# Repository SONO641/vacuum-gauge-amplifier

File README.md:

# amplifier board for thermocouple vacuum gauge

### Description of the control board for vacuum thermocouple gauge.

I found <a href="http://www.belljar.net/tcgauge.htm">
this tutorial</a>  about the operating principle of thermocouple vacuum gauges. I designed the board below based on the article. 

A thermocouple vacuum gauge works by heating a filament at a constant current. The filament’s temperature is higher at a lower pressure because it only loses heat by radiation. The temperature is lower at higher pressure because of the heat loss via the convection of gas in addition to radiation. A thermocouple reads the filament’s temperature and produces a DC signal a function of the temperature difference from the end of the wire. For the gauge I used (KJL-1518) maximum thermocouple voltage is 10mV. I used an instrument amplifier (INA128) to amplify the mV signal by a factor of 330.

The circuit has two parts. One is to supply current to the filament. I used LM317 to limit the current to 16mA. The 5V DC supply for the filament has to be isolated, otherwise thermocouple won't work. I used another DC-DC converter for the instrument amplifier to supply ±9V for INA128. Using this setup, a few mtorr pressure gives 3.7V and 100mtorr 1V between SIG and REF pins. Calibrate the gauve following the artible above.  

A commercial thermocouple gauge controller costs about USD 700 with a display and serial output. Parts for the amplifier board was about USD 25. I use ADS1115 to measure analog signals, and a Raspberry Pi to communicate and log the pressure to a server. Total cost was under USD 100. 

Connect filament +/- to gauge pins 1 and 7, and TC gauge +/- to pin 5/3 of the thermocouple gauge. Apply 5V DC voltage between VIN and GND. Measure voltage between SIG and REF. Applying 5V to enable (EN) to apply current to the filament; pulling EN pin down will shut off the filament current. It may take a few min to filament to heat up, and give steady vacuum readings.

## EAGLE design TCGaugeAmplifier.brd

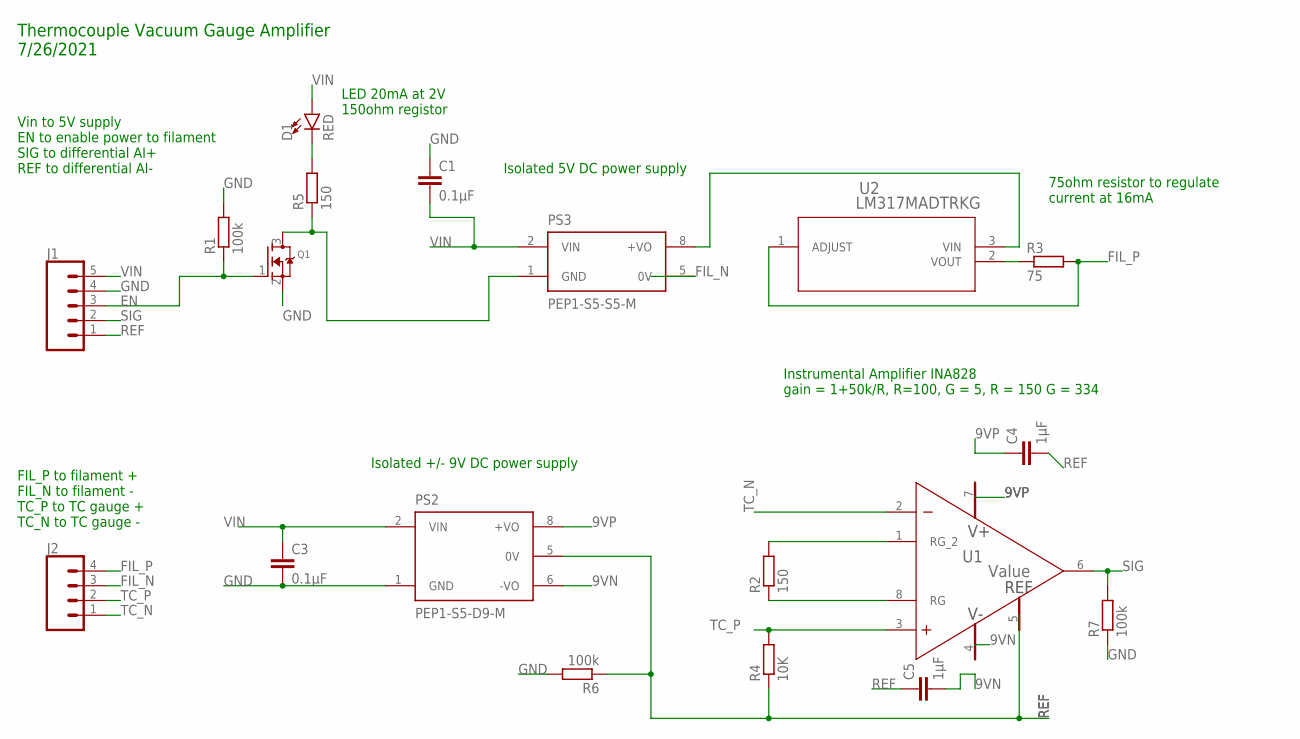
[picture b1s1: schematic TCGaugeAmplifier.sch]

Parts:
C1, C3: 0.1µF; 0805
C4, C5: 1µF; 0805
D1: RED; LED-0603
J1: CONN_05; 1X05
J2: CONN_04; 1X04
PS2: PEP1-S5-D9-M; CONV_PEP1-S5-D9-M
PS3: PEP1-S5-S5-M; CONV_PEP1-S5-S5-M
Q1: MOSFET-NREFLOW; SOT23
R1, R6, R7: 100k; R0805
R2, R5: 150; R0805
R3: 75; R0805
R4: 10K; R0805
U1: Value; D0008A_N
U2: LM317MADTRKG; DPAK-3_ONS

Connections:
9VN: C5.2, PS2.6 (-VO), U1.4 (V-)
9VP: C4.1, PS2.8 (+VO), U1.7 (V+)
EN: J1.3, Q1.1 (G), R1.1
FIL_N: J2.3, PS3.5 (0V)
FIL_P: J2.4, R3.2, U2.1 (ADJUST)
GND: C1.1, C3.2, J1.4, PS2.1 (GND), Q1.2 (S), R1.2, R6.2, R7.1
unnamed: R2.2, U1.1 (RG_2)
unnamed: R2.1, U1.8 (RG)
unnamed: PS3.8 (+VO), U2.3 (VIN)
unnamed: R3.1, U2.2 (VOUT)
unnamed: D1.C, R5.2
unnamed: PS3.1 (GND), Q1.3 (D), R5.1
REF: C4.2, C5.1, J1.1, PS2.5 (0V), R4.1, R6.1, U1.5 (REF)
SIG: J1.2, R7.2, U1.6 (OUT)
TC_N: J2.1, U1.2 (IN-)
TC_P: J2.2, R4.2, U1.3 (IN+)
VIN: C1.2, C3.1, D1.A, J1.5, PS2.2 (VIN), PS3.2 (VIN)

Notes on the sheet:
Vin to 5V supply EN to enable power to filament SIG to differential AI+ REF to differential AI-
FIL_P to filament + FIL_N to filament - TC_P to TC gauge + TC_N to TC gauge -
Isolated 5V DC power supply
Isolated +/- 9V DC power supply
LED 20mA at 2V 150ohm registor
75ohm resistor to regulate current at 16mA
Instrumental Amplifier INA828 gain = 1+50k/R, R=100, G = 5, R = 150 G = 334
Thermocouple Vacuum Gauge Amplifier 7/26/2021

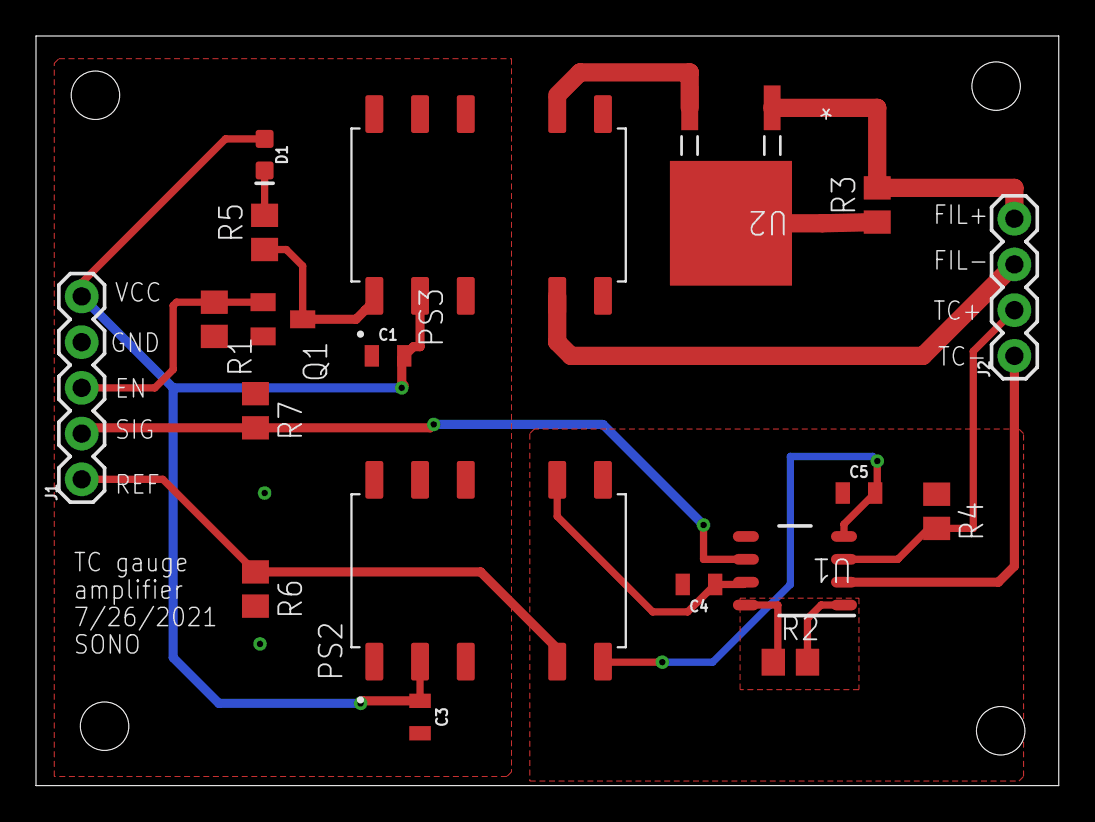
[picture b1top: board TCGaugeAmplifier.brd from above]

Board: 2 copper layers, 56.8 x 41.6 mm, 19 parts (0 on the bottom side), 17 nets.

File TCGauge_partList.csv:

Digi-key Part Number,Description,Unit Price
102-PEP1-S5-D9-M-ND,DC DC CONVERTER +/-9V 1W,4.83
102-PEP1-S5-S5-M-ND,DC DC CONVERTER 5V 1W,4.66
LM317MADTRKGOSCT-ND,IC REG LINEAR POS ADJ 500MA DPAK,0.96
RMCF0805FT100KCT-ND,RES 100K OHM 1% 1/8W 0805,0.027
311-75.0CRCT-ND,RES SMD 75 OHM 1% 1/8W 0805,0.042
P110DACT-ND,RES 110 OHM 0.1% 1/8W 0805,0.31
311-10.0KCRCT-ND,RES SMD 10K OHM 1% 1/8W 0805,0.042
311-3427-1-ND,CAP CER 1UF 16V X5R 0805,0.13
478-10836-1-ND,CAP CER 0.1UF 50V X7R 0805,0.076
296-26057-1-ND,Texas Instruments IC INST AMP 1 CIRCUIT 8SOIC,9.36
732-4980-1-ND,LED GREEN CLEAR 0603 SMD,0.15
TSM240N03CX RFG,MOSFET N-CHANNEL 30V 6.5A SOT23,0.94

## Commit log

2022-07-30 eagle .brd file
    board design file for Eagle
2022-08-04 Create LICENSE
2022-08-04 Create LICENSE
    license from template

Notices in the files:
parts and their libraries:
SparkFun-Capacitors: Licensing: Creative Commons ShareAlike 4.0 International - https://creativecommons.org/licenses/by-sa/4.0
COPYRIGHT: Copyright (C) 2016 Accelerated Designs. All rights reserved
